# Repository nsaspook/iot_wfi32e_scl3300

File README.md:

# iot_wfi32e_scl3300
uses a modified version of the Paho MQTT Client
sends SCL3300 accel and angle data to mateq84/data/imu MQTT topic

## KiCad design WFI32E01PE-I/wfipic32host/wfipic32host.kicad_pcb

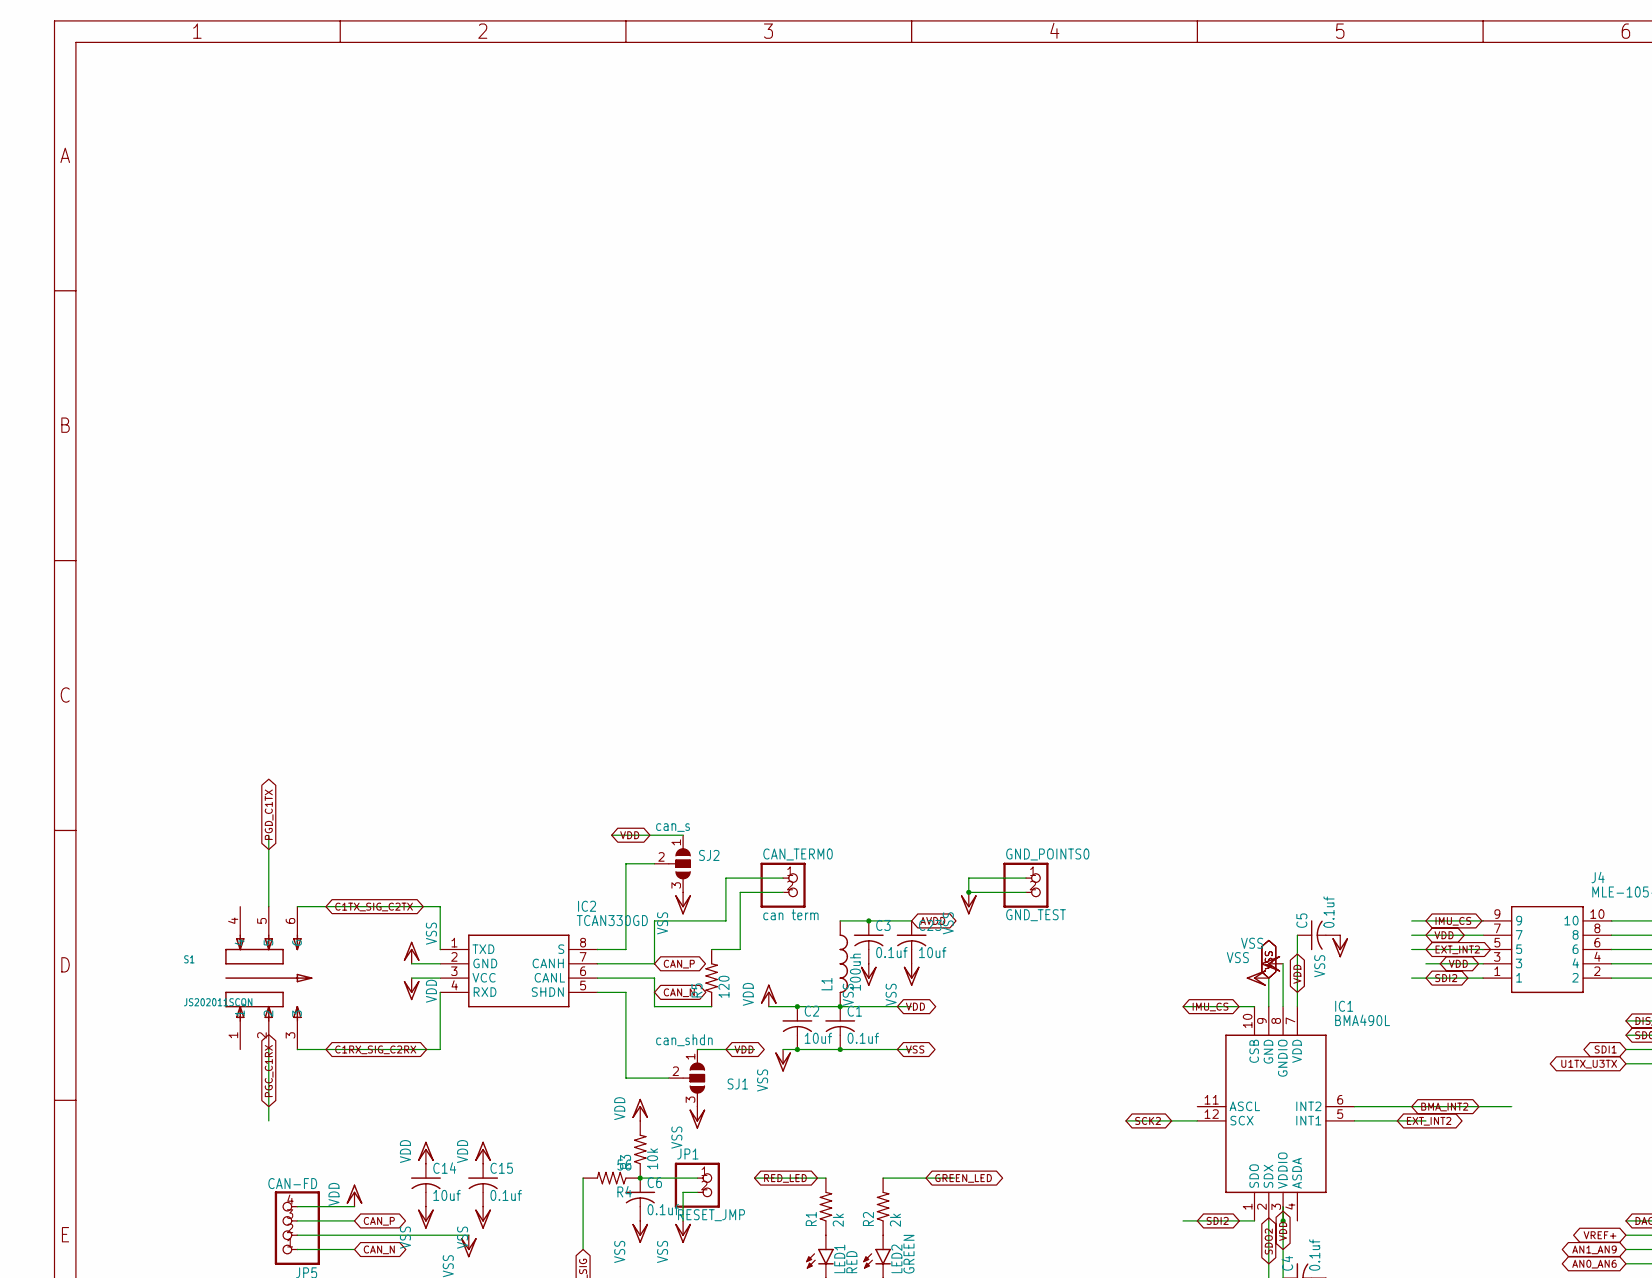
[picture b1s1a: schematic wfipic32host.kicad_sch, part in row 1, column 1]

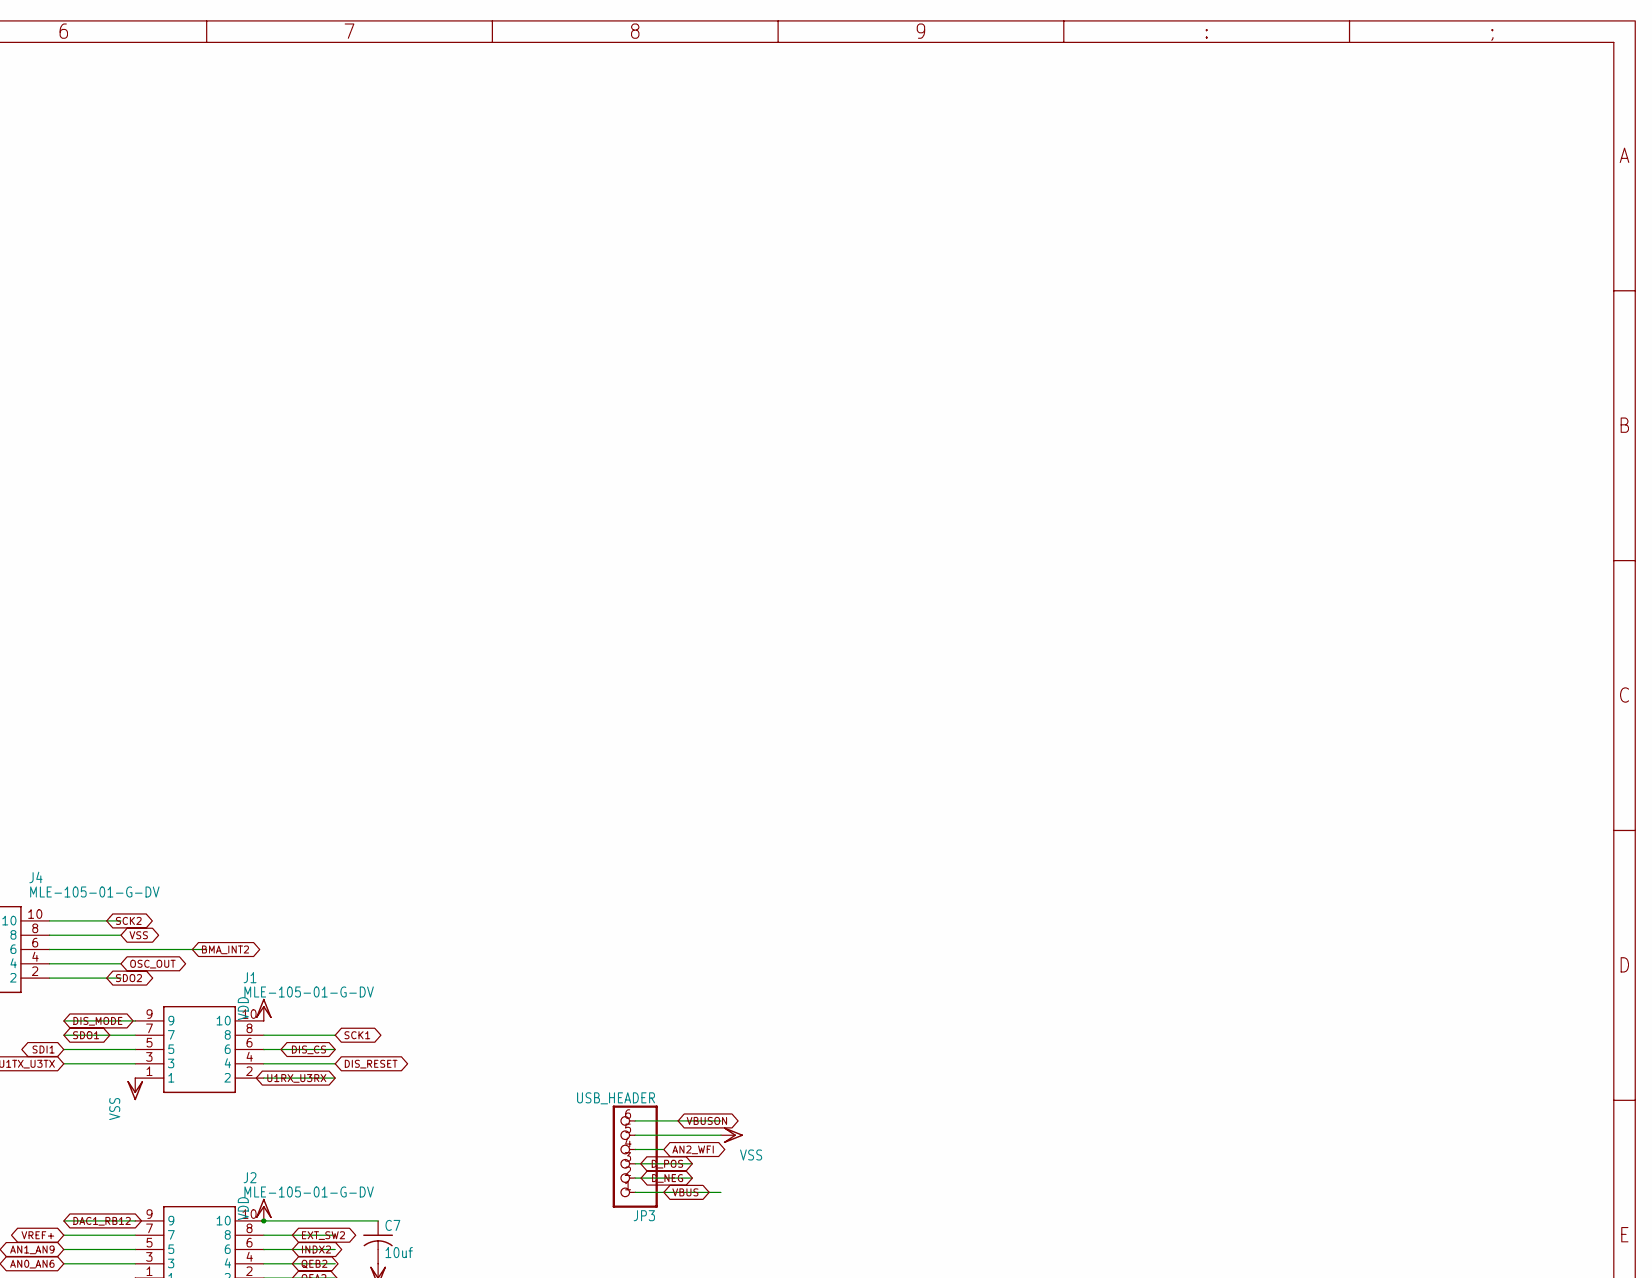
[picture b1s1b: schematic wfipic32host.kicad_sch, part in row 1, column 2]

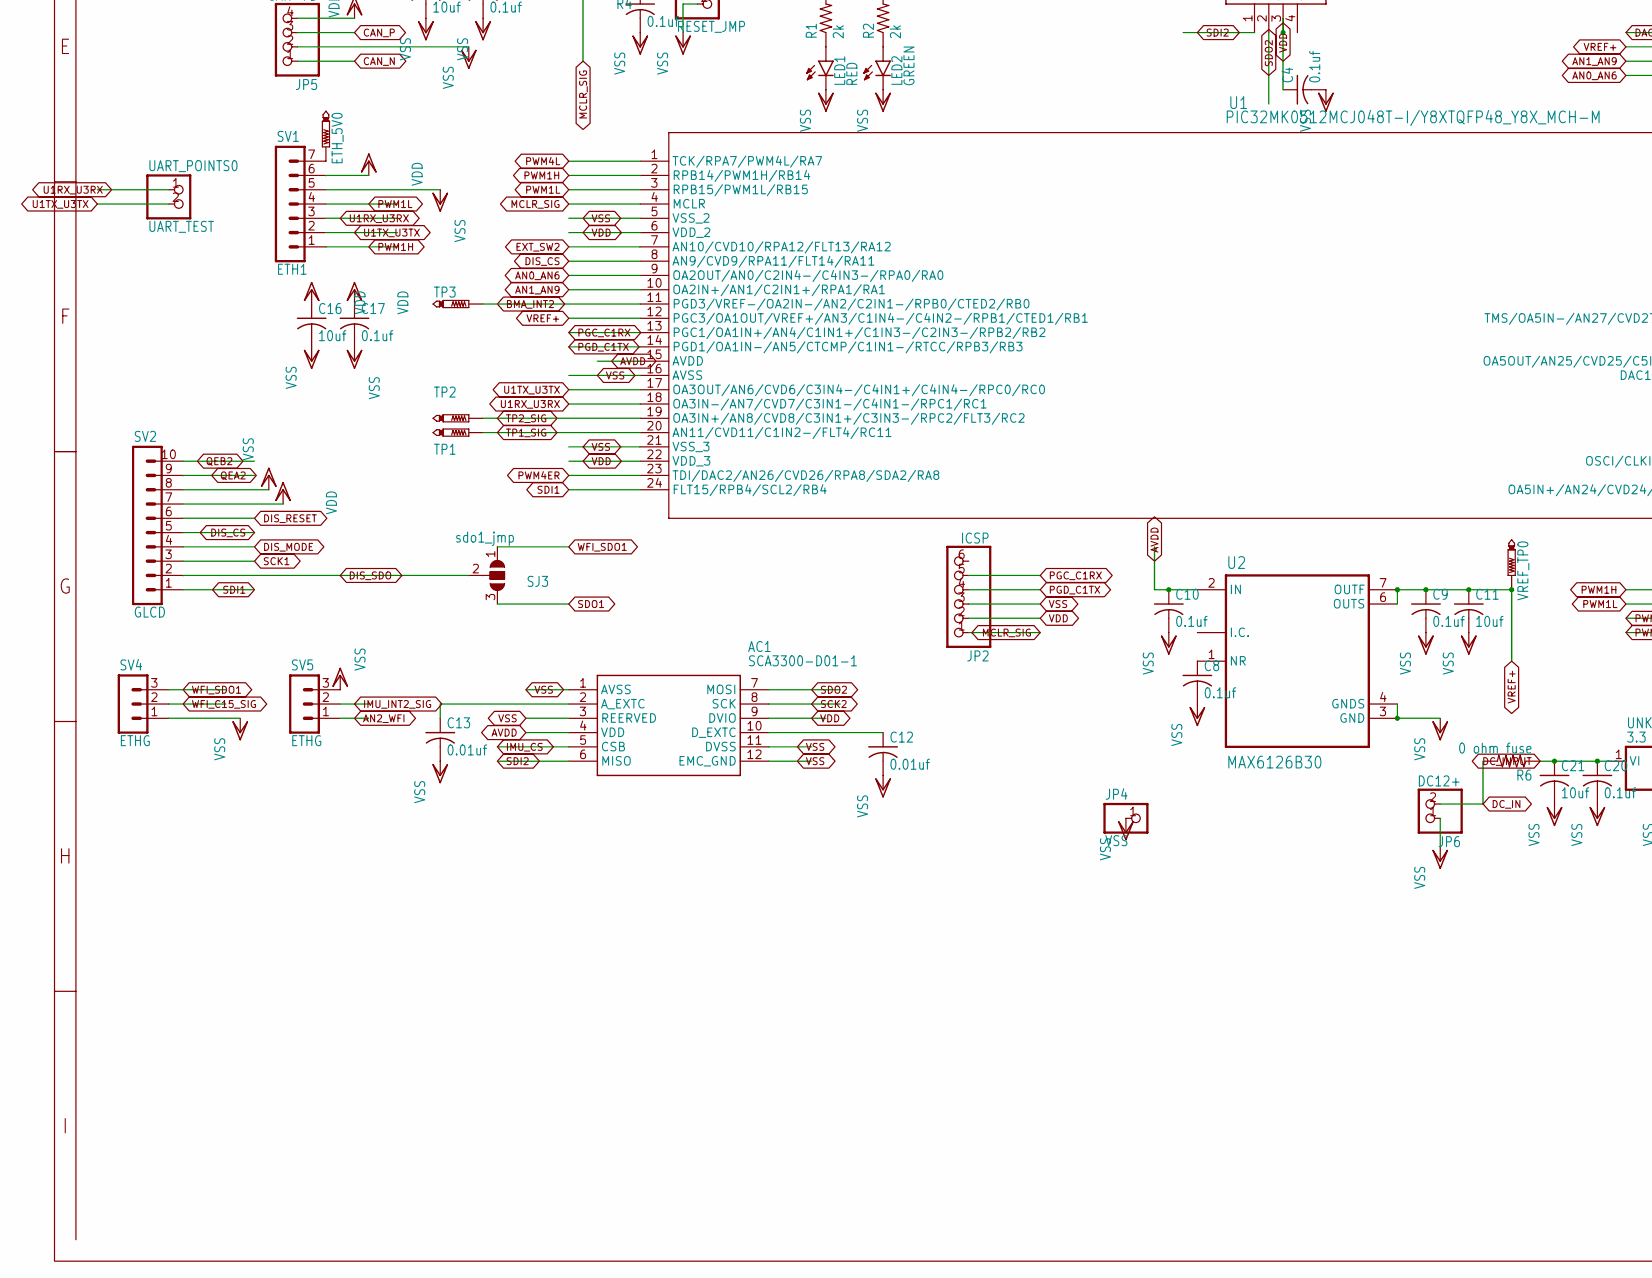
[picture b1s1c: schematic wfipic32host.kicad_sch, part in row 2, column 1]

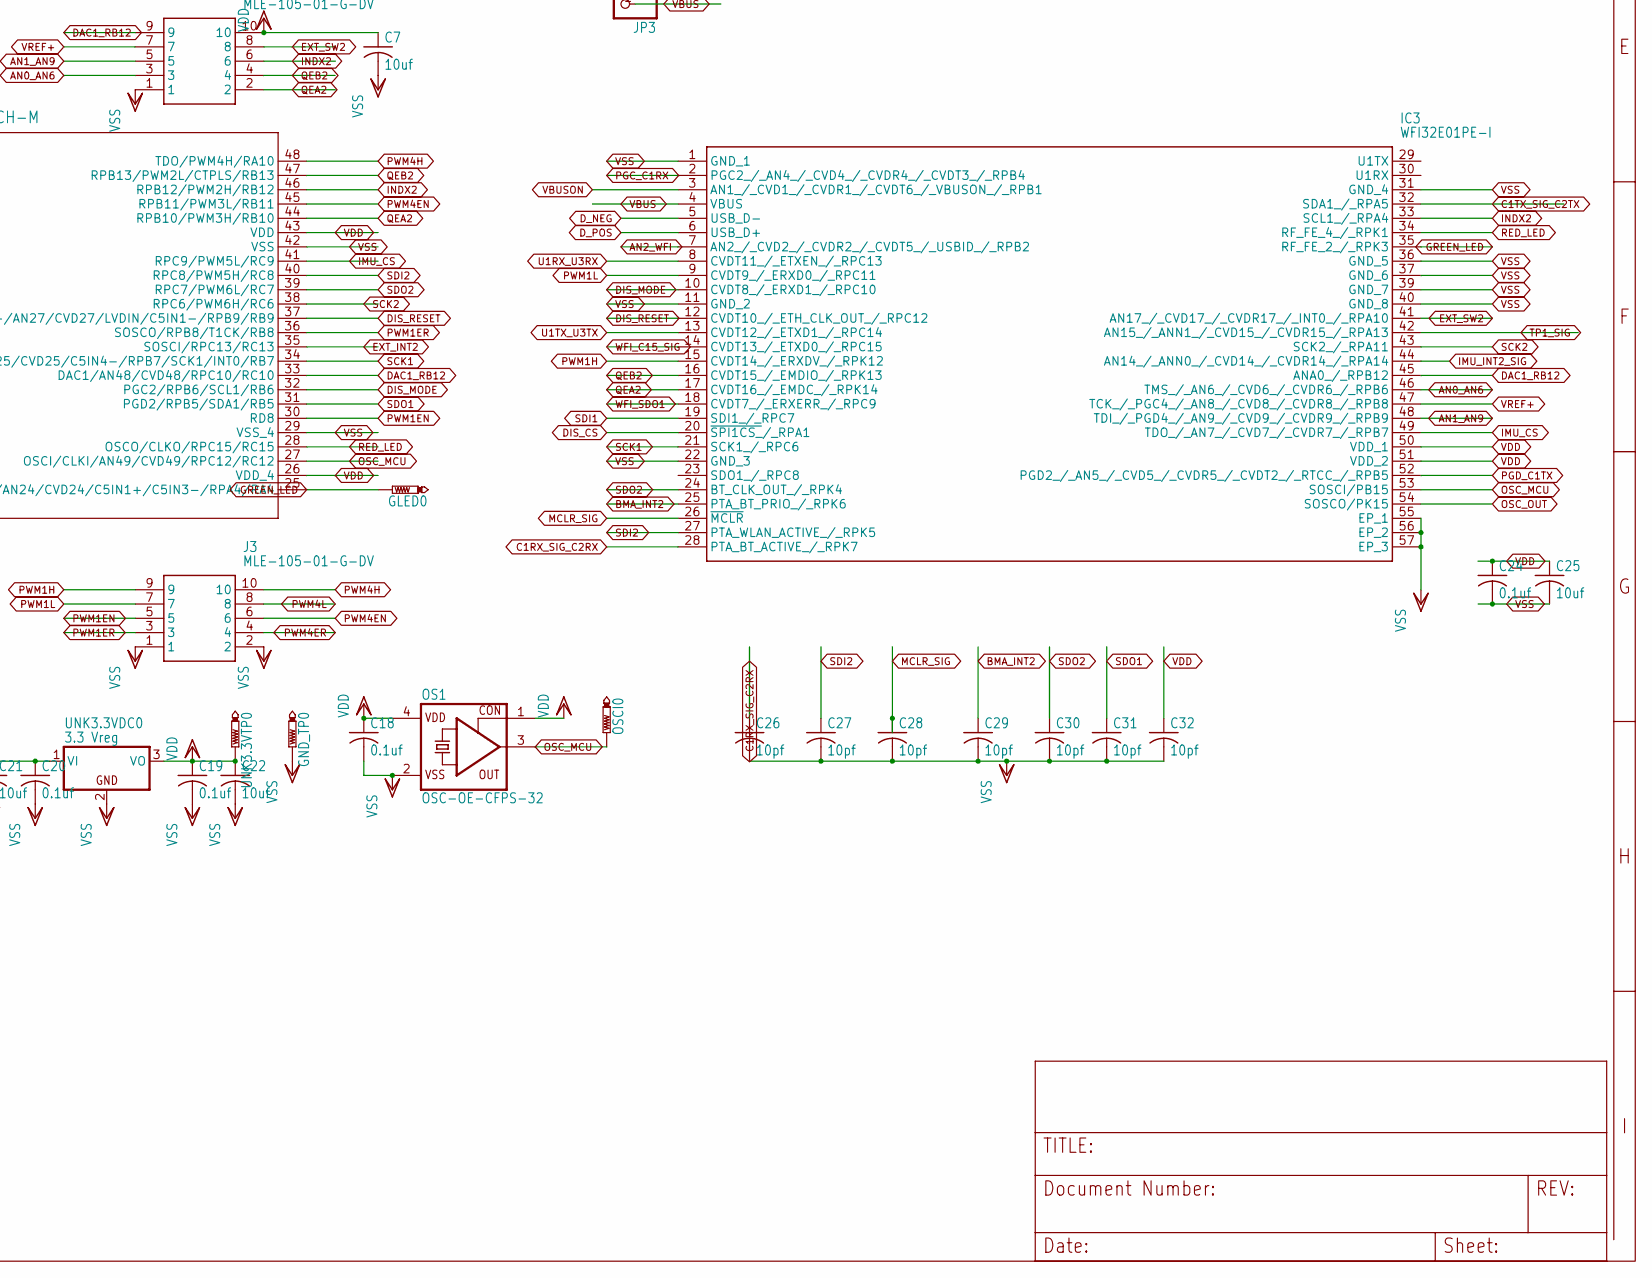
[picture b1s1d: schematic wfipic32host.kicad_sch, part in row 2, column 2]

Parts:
AC1: SCA3300-D01-1; SCA3300
C1, C3, C4, C5, C6, C8, C9, C10, C15, C17, C18, C19, C20, C24: 0.1uf; C0805
C2, C7, C11, C14, C16, C21, C22, C23, C25: 10uf; C0805
C12, C13: 0.01uf; C0805
C26, C27, C28, C29, C30, C31, C32: 10pf; C0402
CAN_TERM0: can term; 1X02
ETH_5V0: PTR1PAD1-13; P1-13
GLED0: PTR1PAD1-13; P1-13
GND_POINTS0: GND_TEST; 1X02
GND_TP0: PTR1PAD1-13; P1-13
IC1: BMA490L; MANUFACTURER_PART_NUMBER BMA490L; MOUSER_PART_NUMBER 262-BMA490L
IC2: TCAN330GD; SOIC127P600X175-8N; MANUFACTURER_PART_NUMBER TCAN330GD; MOUSER_PART_NUMBER 595-TCAN330GD
IC3: WFI32E01PE-I; WFI32E01PEI; MANUFACTURER_PART_NUMBER WFI32E01PE-I; MOUSER_PART_NUMBER 579-WFI32E01PE-I
J1, J2, J3, J4: MLE-105-01-G-DV; MANUFACTURER_PART_NUMBER MLE-105-01-G-DV; MOUSER_PART_NUMBER 200-MLE10501GDV
JP1: RESET_JMP; 1X02
JP2: ICSP; 1X06
JP3: USB_HEADER; 1X06
JP4: VSS; 1X01
JP5: CAN-FD; 1X04_90
JP6: DC12+; 1X02
L1: 100uh; L3216C
LED1: RED; CHIPLED_0603
LED2: GREEN; CHIPLED_0603
OS1: OSC-OE-CFPS-32; 7.2X5.2-4-PAD
OSCI0: PTR1PAD1-13; P1-13
R1, R2: 2k; M0805
R3: 10k; M0805
R4: 56; M0805
R5: 120; M0805
R6: 0 ohm fuse; M1206
S1: JS202011SCQN; SW_JS202011SCQN
SJ1: can_shdn; SJ_2
SJ2: can_s; SJ_2
SJ3: sdo1_jmp; SJ_2
SV1: ETH1; MA07-1
SV2: GLCD; MA10-1
SV4, SV5: ETHG; MA03-1
TP1, TP2, TP3: PTR1PAD1-13; P1-13
U1: PIC32MK0512MCJ048T-I/Y8XTQFP48_Y8X_MCH-M; TQFP48_Y8X_MCH-M; MANUFACTURER_PART_NUMBER PIC32MK0512MCJ048T-I/Y8X
U2: MAX6126B30; SOP65P490X110-8N; DIGI-KEY_PART_NUMBER MAX6126B30+T-ND
UART_POINTS0: UART_TEST; 1X02
UNK3.3VDC0: 3.3 Vreg; TO220V
UNK3.3VTP0: PTR1PAD1-13; P1-13
VREF_TP0: PTR1PAD1-13; P1-13

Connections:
AN0_AN6: IC3.46 (TMS_/_AN6_/_CVD6_/_CVDR6_/_RPB6), J2.3, U1.9 (OA2OUT/AN0/C2IN4-/C4IN3-/RPA0/RA0)
AN1_AN9: IC3.48 (TDI_/_PGD4_/_AN9_/_CVD9_/_CVDR9_/_RPB9), J2.5, U1.10 (OA2IN+/AN1/C2IN1+/RPA1/RA1)
AN2_WFI: IC3.7 (AN2_/_CVD2_/_CVDR2_/_CVDT5_/_USBID_/_RP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), JP3.4, SV5.1
AVDD: AC1.4 (VDD), C3.1, C10.1, C23.1, L1.1, U1.15 (AVDD), U2.2 (IN)
BMA_INT2: C29.1, IC1.6 (INT2), IC3.25 (PTA_BT_PRIO_/_RPK6), J4.6, TP3.TP, U1.11 (PGD3/VREF-/OA2IN-/AN2/C2IN1-/RPB0/CTED2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)
C1RX_SIG_C2RX: C26.1, IC2.4 (RXD), IC3.28 (PTA_BT_ACTIVE_/_RPK7), S1.3
C1TX_SIG_C2TX: IC2.1 (TXD), IC3.32 (SDA1_/_RPA5), S1.6
CAN_N: IC2.6 (CANL), JP5.1, R5.1
CAN_P: CAN_TERM0.1, IC2.7 (CANH), JP5.3
DAC1_RB12: IC3.45 (ANA0_/_RPB12), J2.9, U1.33 (DAC1/AN48/CVD48/RPC10/RC10)
DC_IN: JP6.2, R6.2
DC_INPUT: C20.1, C21.1, R6.1, UNK3.3VDC0.1 (VI)
DIS_CS: IC3.20 (~SPI1CS_/_RPA1), J1.6, SV2.5, U1.8 (AN9/CVD9/RPA11/FLT14/RA11)
DIS_MODE: IC3.10 (CVDT8_/_ERXD1_/_RPC10), J1.9, SV2.4, U1.32 (PGC2/RPB6/SCL1/RB6)
DIS_RESET: IC3.12 (CVDT10_/_ETH_CLK_OUT_/_RPC12), J1.4, SV2.6, U1.37 (TMS/OA5IN-/AN27/CVD27/LVDIN/C5IN1-/RPB9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)
DIS_SDO: SJ3.2, SV2.2
D_NEG: IC3.5 (USB_D-), JP3.2
D_POS: IC3.6 (USB_D+), JP3.3
EXT_INT2: IC1.5 (INT1), J4.5, U1.35 (SOSCI/RPC13/RC13)
EXT_SW2: IC3.41 (AN17_/_CVD17_/_CVDR17_/_INT0_/_RPA10), J2.8, U1.7 (AN10/CVD10/RPA12/FLT13/RA12)
GREEN_LED: GLED0.TP, IC3.35 (RF_FE_2_/_RPK3), R2.2, U1.25 (OA5IN+/AN24/CVD24/C5IN1+/C5IN3-/RPA4/RA4)
IMU_CS: AC1.5 (CSB), IC1.10 (CSB), IC3.49 (TDO_/_AN7_/_CVD7_/_CVDR7_/_RPB7), J4.9, U1.41 (RPC9/PWM5L/RC9)
IMU_INT2_SIG: IC3.44 (AN14_/_ANN0_/_CVD14_/_CVDR14_/_RPA14), SV5.2
INDX2: IC3.33 (SCL1_/_RPA4), J2.6, U1.46 (RPB12/PWM2H/RB12)
MCLR_SIG: C28.1, IC3.26 (~MCLR), JP2.1, R4.2, U1.4 (MCLR)
unnamed: LED1.A, R1.1
unnamed: LED2.A, R2.1
unnamed: C6.1, JP1.1, R3.1, R4.1
unnamed: C8.1, U2.1 (NR)
unnamed: AC1.10 (D_EXTC), C12.1
unnamed: ETH_5V0.TP, SV1.7
unnamed: AC1.2 (A_EXTC), C13.1
unnamed: IC2.5 (SHDN), SJ1.2
unnamed: IC2.8 (S), SJ2.2
unnamed: CAN_TERM0.2, R5.2
OSC_MCU: IC3.53 (SOSCI/PB15), OS1.3 (OUT), OSCI0.TP, U1.27 (OSCI/CLKI/AN49/CVD49/RPC12/RC12)
OSC_OUT: IC3.54 (SOSCO/PK15), J4.4
PGC_C1RX: IC3.2 (PGC2_/_AN4_/_CVD4_/_CVDR4_/_CVDT3_/_RPB4), JP2.5, S1.2, U1.13 (PGC1/OA1IN+/AN4/C1IN1+/C1IN3-/C2IN3-/RP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)
PGD_C1TX: IC3.52 (PGD2_/_AN5_/_CVD5_/_CVDR5_/_CVDT2_/_RTC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), JP2.4, S1.5, U1.14 (PGD1/OA1IN-/AN5/CTCMP/C1IN1-/RTCC/RPB3/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)
PWM1EN: J3.5, U1.30 (RD8)
PWM1ER: J3.3, U1.36 (SOSCO/RPB8/T1CK/RB8)
PWM1H: IC3.15 (CVDT14_/_ERXDV_/_RPK12), J3.9, SV1.1, U1.2 (RPB14/PWM1H/RB14)
PWM1L: IC3.9 (CVDT9_/_ERXD0_/_RPC11), J3.7, SV1.4, U1.3 (RPB15/PWM1L/RB15)
PWM4EN: J3.6, U1.45 (RPB11/PWM3L/RB11)
PWM4ER: J3.4, U1.23 (TDI/DAC2/AN26/CVD26/RPA8/SDA2/RA8)
PWM4H: J3.10, U1.48 (TDO/PWM4H/RA10)
PWM4L: J3.8, U1.1 (TCK/RPA7/PWM4L/RA7)
QEA2: IC3.17 (CVDT16_/_EMDC_/_RPK14), J2.2, SV2.9, U1.44 (RPB10/PWM3H/RB10)
QEB2: IC3.16 (CVDT15_/_EMDIO_/_RPK13), J2.4, SV2.10, U1.47 (RPB13/PWM2L/CTPLS/RB13)
RED_LED: IC3.34 (RF_FE_4_/_RPK1), R1.2, U1.28 (OSCO/CLKO/RPC15/RC15)
SCK1: IC3.21 (SCK1_/_RPC6), J1.8, SV2.3, U1.34 (OA5OUT/AN25/CVD25/C5IN4-/RPB7/SCK1/INT0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)
SCK2: AC1.8 (SCK), IC1.12 (SCX), IC3.43 (SCK2_/_RPA11), J4.10, U1.38 (RPC6/PWM6H/RC6)
SDI1: IC3.19 (SDI1_/_RPC7), J1.5, SV2.1, U1.24 (FLT15/RPB4/SCL2/RB4)
SDI2: AC1.6 (MISO), C27.1, IC1.1 (SDO), IC3.27 (PTA_WLAN_ACTIVE_/_RPK5), J4.1, U1.40 (RPC8/PWM5H/RC8)
SDO1: C31.1, J1.7, SJ3.3, U1.31 (PGD2/RPB5/SDA1/RB5)
SDO2: AC1.7 (MOSI), C30.1, IC1.2 (SDX), IC3.24 (BT_CLK_OUT_/_RPK4), J4.2, U1.39 (RPC7/PWM6L/RC7)
TP1_SIG: IC3.42 (AN15_/_ANN1_/_CVD15_/_CVDR15_/_RPA13), TP1.TP, U1.20 (AN11/CVD11/C1IN2-/FLT4/RC11)
TP2_SIG: TP2.TP, U1.19 (OA3IN+/AN8/CVD8/C3IN1+/C3IN3-/RPC2/FLT3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)
U1RX_U3RX: IC3.8 (CVDT11_/_ETXEN_/_RPC13), J1.2, SV1.3, U1.18 (OA3IN-/AN7/CVD7/C3IN1-/C4IN1-/RPC1/RC1), UART_POINTS0.1
U1TX_U3TX: IC3.13 (CVDT12_/_ETXD1_/_RPC14), J1.3, SV1.2, U1.17 (OA3OUT/AN6/CVD6/C3IN4-/C4IN1+/C4IN4-/RP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), UART_POINTS0.2
VBUS: IC3.4 (VBUS), JP3.1
VBUSON: IC3.3 (AN1_/_CVD1_/_CVDR1_/_CVDT6_/_VBUSON_/_R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), JP3.6
VDD: AC1.9 (DVIO), C1.1, C2.1, C4.1, C5.1, C7.1, C14.1, C15.1, C16.1, C17.1, C18.1, C19.1, C22.1, C24.1, C25.1, C32.1, IC1.3 (VDDIO), IC1.7 (VDD), IC2.3 (VCC), IC3.50 (VDD_1), IC3.51 (VDD_2), J1.10, J2.10, J4.3, J4.7, JP2.2, JP5.4, L1.2, OS1.1 (CON), OS1.4 (VDD), R3.2, SJ1.1, SJ2.1, SV1.6, SV2.7, U1.6 (VDD_2), U1.22 (VDD_3), U1.26 (VDD_4), U1.43 (VDD), UNK3.3VDC0.3 (VO), UNK3.3VTP0.TP
VREF+: C9.1, C11.1, IC3.47 (TCK_/_PGC4_/_AN8_/_CVD8_/_CVDR8_/_RPB8), J2.7, U1.12 (PGC3/OA1OUT/VREF+/AN3/C1IN4-/C4IN2-/RPB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), U2.6 (OUTS), U2.7 (OUTF), VREF_TP0.TP
VSS: AC1.1 (AVSS), AC1.3 (REERVED), AC1.11 (DVSS), AC1.12 (EMC_GND), C1.2, C2.2, C3.2, C4.2, C5.2, C6.2, C7.2, C8.2, C9.2, C10.2, C11.2, C12.2, C13.2, C14.2, C15.2, C16.2, C17.2, C18.2, C19.2, C20.2, C21.2, C22.2, C23.2, C24.2, C25.2, C26.2, C27.2, C28.2, C29.2, C30.2, C31.2, C32.2, GND_POINTS0.1, GND_POINTS0.2, GND_TP0.TP, IC1.8 (GNDIO), IC1.9 (GND), IC2.2 (GND), IC3.1 (GND_1), IC3.11 (GND_2), IC3.22 (GND_3), IC3.31 (GND_4), IC3.36 (GND_5), IC3.37 (GND_6), IC3.39 (GND_7), IC3.40 (GND_8), IC3.55 (EP_1), IC3.56 (EP_2), IC3.57 (EP_3), J1.1, J2.1, J3.1, J3.2, J4.8, JP1.2, JP2.3, JP3.5, JP4.1, JP5.2, JP6.1, LED1.C, LED2.C, OS1.2 (VSS), SJ1.3, SJ2.3, SV1.5, SV2.8, SV4.1, SV5.3, U1.5 (VSS_2), U1.16 (AVSS), U1.21 (VSS_3), U1.29 (VSS_4), U1.42 (VSS), U2.3 (GND), U2.4 (GNDS), UNK3.3VDC0.2 (GND)
WFI_C15_SIG: IC3.14 (CVDT13_/_ETXD0_/_RPC15), SV4.2
WFI_SDO1: IC3.18 (CVDT7_/_ERXERR_/_RPC9), SJ3.1, SV4.3

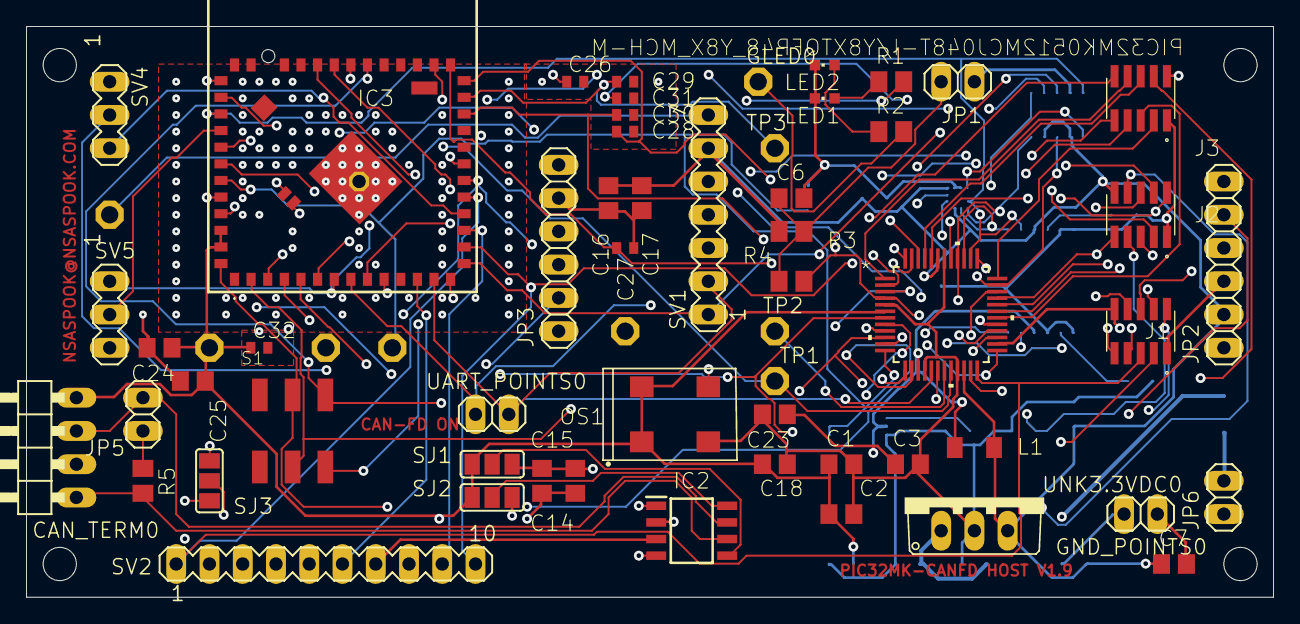
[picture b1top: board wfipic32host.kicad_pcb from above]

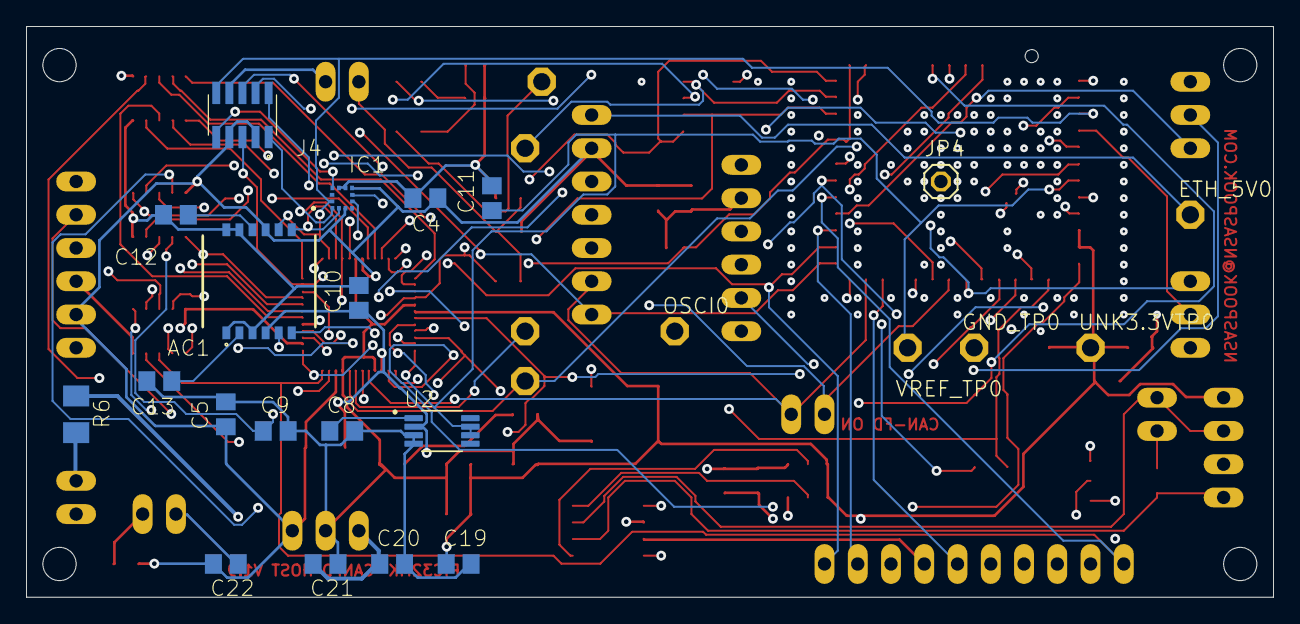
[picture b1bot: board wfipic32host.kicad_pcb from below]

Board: 4 copper layers, 95.2 x 43.6 mm, 84 parts (23 on the bottom side), 67 nets.

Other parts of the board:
UNK_HOLE_0: dummyfp0
UNK_HOLE_1: dummyfp1
UNK_HOLE_2: dummyfp2
UNK_HOLE_3: dummyfp3
UNK_HOLE_4: dummyfp4

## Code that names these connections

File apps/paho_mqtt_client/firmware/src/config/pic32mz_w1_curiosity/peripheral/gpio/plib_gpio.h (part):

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// *****************************************************************************


/*** Macros for GPIO_RC15 pin ***/
#define GPIO_RC15_Set()               (LATCSET = (1U<<15))
#define GPIO_RC15_Clear()             (LATCCLR = (1U<<15))
#define GPIO_RC15_Toggle()            (LATCINV= (1U<<15))
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#define GPIO_RC15_InputEnable()       (TRISCSET = (1U<<15))
#define GPIO_RC15_Get()               ((PORTC >> 15) & 0x1U)
#define GPIO_RC15_GetLatch()          ((LATC >> 15) & 0x1U)
#define GPIO_RC15_PIN                  GPIO_PIN_RC15

/*** Macros for QEB2_SIG pin ***/
#define QEB2_SIG_Set()               (LATKSET = (1U<<13))
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#define QEB2_SIG_GetLatch()          ((LATK >> 13) & 0x1U)
#define QEB2_SIG_PIN                  GPIO_PIN_RK13

/*** Macros for DIS_CS pin ***/
#define DIS_CS_Set()               (LATASET = (1U<<1))
#define DIS_CS_Clear()             (LATACLR = (1U<<1))
#define DIS_CS_Toggle()            (LATAINV= (1U<<1))
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#define DIS_CS_InputEnable()       (TRISASET = (1U<<1))
#define DIS_CS_Get()               ((PORTA >> 1) & 0x1U)
#define DIS_CS_GetLatch()          ((LATA >> 1) & 0x1U)
#define DIS_CS_PIN                  GPIO_PIN_RA1

/*** Macros for EXT_SW1 pin ***/
#define EXT_SW1_Set()               (LATASET = (1U<<4))
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#define AN1_T_GetLatch()          ((LATB >> 9) & 0x1U)
#define AN1_T_PIN                  GPIO_PIN_RB9

/*** Macros for IMU_CS pin ***/
#define IMU_CS_Set()               (LATBSET = (1U<<7))
#define IMU_CS_Clear()             (LATBCLR = (1U<<7))
#define IMU_CS_Toggle()            (LATBINV= (1U<<7))
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#define IMU_CS_InputEnable()       (TRISBSET = (1U<<7))
#define IMU_CS_Get()               ((PORTB >> 7) & 0x1U)
#define IMU_CS_GetLatch()          ((LATB >> 7) & 0x1U)
#define IMU_CS_PIN                  GPIO_PIN_RB7

/*** Macros for PWM1L_T pin ***/
#define PWM1L_T_Get()               ((PORTC >> 11) & 0x1U)
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#define VREF_IN_GetLatch()          ((LATB >> 8) & 0x1U)
#define VREF_IN_PIN                  GPIO_PIN_RB8

/*** Macros for GPIO_RB4 pin ***/
#define GPIO_RB4_Set()               (LATBSET = (1U<<4))
#define GPIO_RB4_Clear()             (LATBCLR = (1U<<4))
#define GPIO_RB4_Toggle()            (LATBINV= (1U<<4))
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#define GPIO_RB4_InputEnable()       (TRISBSET = (1U<<4))
#define GPIO_RB4_Get()               ((PORTB >> 4) & 0x1U)
#define GPIO_RB4_GetLatch()          ((LATB >> 4) & 0x1U)
#define GPIO_RB4_PIN                  GPIO_PIN_RB4

/*** Macros for DIS_MODE pin ***/
#define DIS_MODE_Set()               (LATCSET = (1U<<10))
#define DIS_MODE_Clear()             (LATCCLR = (1U<<10))
#define DIS_MODE_Toggle()            (LATCINV= (1U<<10))
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#define DIS_MODE_InputEnable()       (TRISCSET = (1U<<10))
#define DIS_MODE_Get()               ((PORTC >> 10) & 0x1U)
#define DIS_MODE_GetLatch()          ((LATC >> 10) & 0x1U)
#define DIS_MODE_PIN                  GPIO_PIN_RC10

/*** Macros for DIS_RESET pin ***/
#define DIS_RESET_Set()               (LATCSET = (1U<<12))
#define DIS_RESET_Clear()             (LATCCLR = (1U<<12))
#define DIS_RESET_Toggle()            (LATCINV= (1U<<12))
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#define DIS_RESET_InputEnable()       (TRISCSET = (1U<<12))
#define DIS_RESET_Get()               ((PORTC >> 12) & 0x1U)
#define DIS_RESET_GetLatch()          ((LATC >> 12) & 0x1U)
#define DIS_RESET_PIN                  GPIO_PIN_RC12


// *****************************************************************************
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
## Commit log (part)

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2023-12-04 update for JCLPCB
2023-12-12 first board spin testing
2023-12-12 working prototype PCB
2023-12-13 temp sensor
2024-01-05 ipv6 update
2025-04-14 refresh
2025-04-14 rename project
2025-04-16 update to latest harmony with wolf still at 5.4.0 for source

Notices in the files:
apps/paho_mqtt_client/firmware/src/config/pic32mz_w1_curiosity/peripheral/gpio/plib_gpio.h:
Copyright (C) 2019 Microchip Technology Inc. and its subsidiaries.
parts and their libraries:
COPYRIGHT: Copyright (C) 2022 Ultra Librarian. All rights reserved.
